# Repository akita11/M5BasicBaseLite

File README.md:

# M5BasicBaseLite

M5Stackの上部本体(Core Basic)にとりつけて、以下のようなM5GO/Fireの機能やそれ以外の機能を追加できる底板（ベースボード）用の拡張基板です。
[M5GOBaseLite](https://github.com/akita11/M5GOBaseLite)の後継機で、基本的な機能・回路は同一で、裏面のメスMbusコネクタが使えるようになりました。
- Groveコネクタ(PortA(2個), PortB, PortC, PortD, PortE)（PortA/B/CはM5Stack純正のものと同等です。PortD/EはM5Stack純正品にはありませんが、UI Flowで使用することができるポートです）
- 左右5個ずつのNeoPixel (SK6812)（オプション）
- LiPoバッテリ接続端子（オプション）

# 使い方
1. M5Stackの本体(Core、底板を外した状態)に本ボードを差し込みます。
2. M5Stackのプログラムから、Groveコネクタに接続したセンサ類を使用します。
   - 各Groveコネクタのピン配置は以下の通り（中央寄りのVDDから近い側、遠い側の順）
     - PortA: GPIO21(SDA), GPIO22(SCL)
     - PortB: GPIO26, GPIO36
     - PortC: GPIO17(TXD2), GPIO16(RXD2)
     - PortD: GPIO35, GPIO34
     - PortE: GPIO13, GPIO5
   - （オプション）左右のNeoPixelの制御信号はGPIO15につながっています。UI Flowでは、Hardware→RGB LED、から使用できます

# 底面カバー

[M5GOBaseLite](https://github.com/akita11/M5GOBaseLite)用のカバーを使用できます。

# Author

Junichi Akita (@akita11, akita@ifdl.jp)

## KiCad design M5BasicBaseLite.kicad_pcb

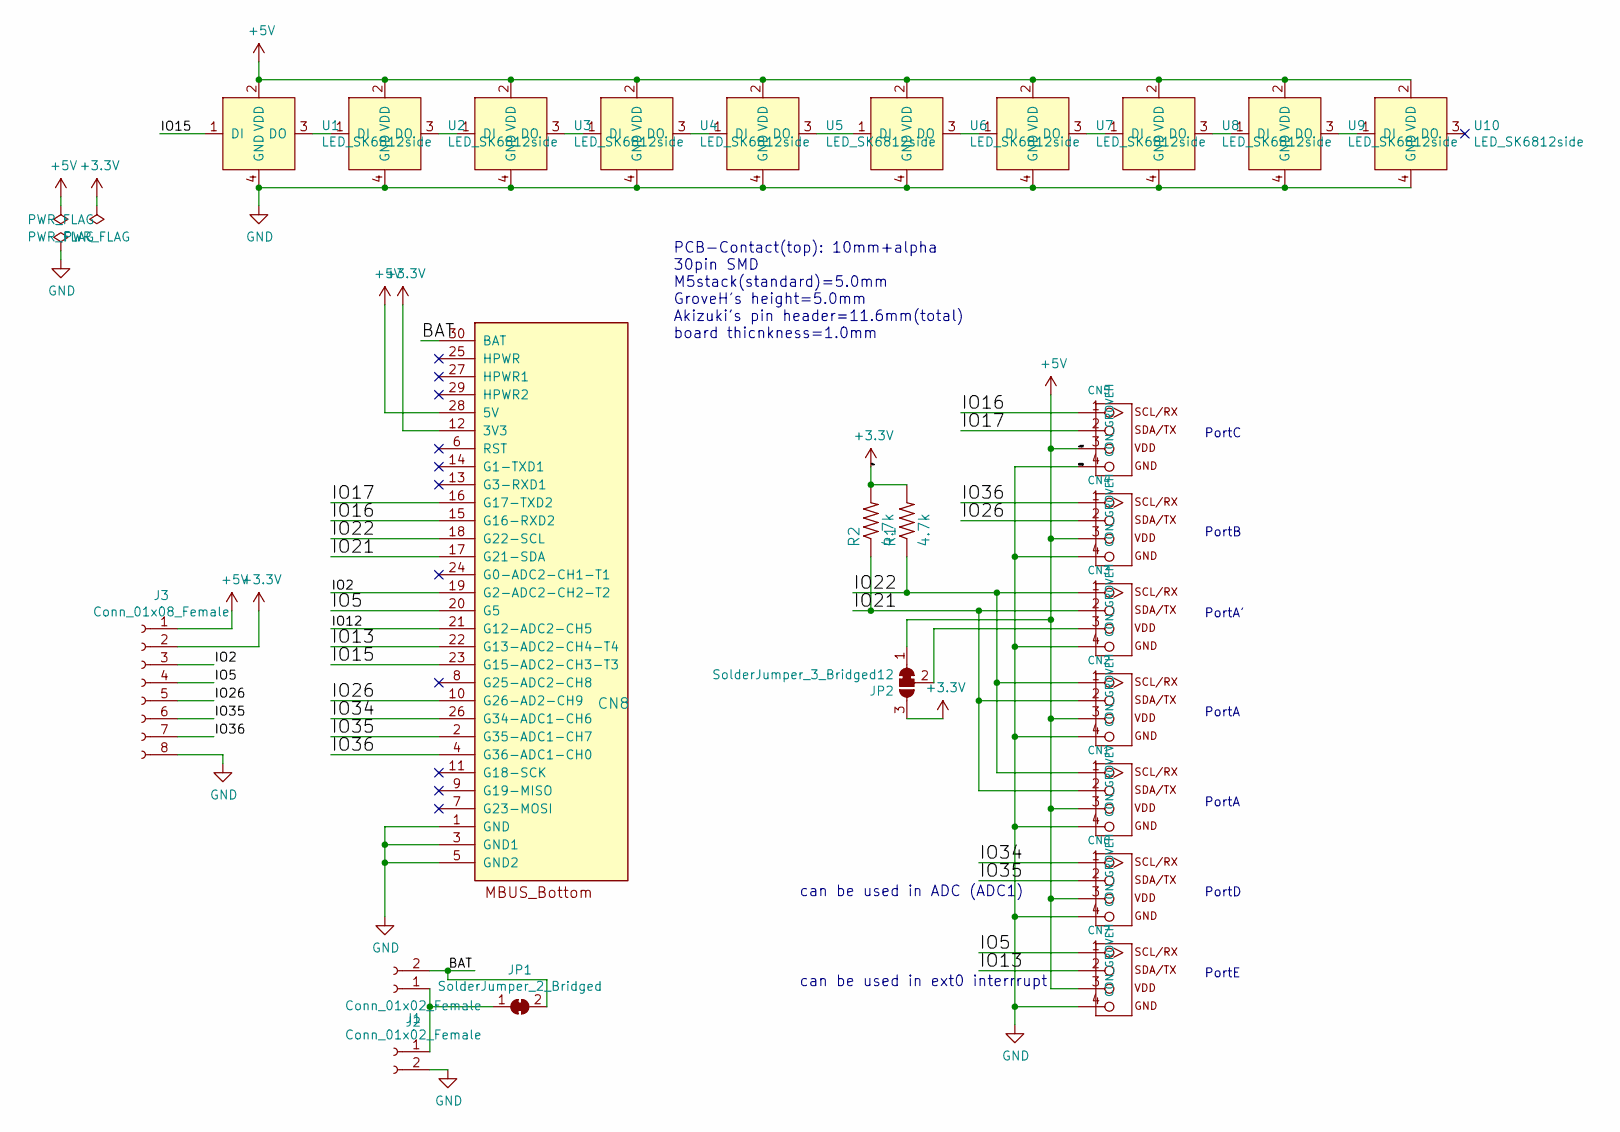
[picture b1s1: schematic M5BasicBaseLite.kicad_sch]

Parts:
CN1: CON_GROVEV; CON_GROVE_V
CN2, CN3, CN4, CN5, CN6, CN7: CON_GROVEH; CON_GROVE_H
CN8: MBUS_bottom; PinSocket_2x15_P2.54mm_Vertical_SMD
J1: Conn_01x02_Female; JST_PH_S2B-PH-K_1x02_P2.00mm_Horizontal
J2: Conn_01x02_Female; PinHeader_1x02_P2.54mm_Horizontal
J3: Conn_01x08_Female; PinSocket_1x08_P2.54mm_Horizontal
JP1: SolderJumper_2_Bridged; SolderJumper-2_P1.3mm_Bridged_Pad1.0x1.5mm
JP2: SolderJumper_3_Bridged12; SolderJumper-3_P1.3mm_Bridged2Bar12_Pad1.0x1.5mm
R1, R2: 4.7k; 0603
U1, U2, U3, U4, U5, U6, U7, U8, U9, U10: LED_SK6812side; LED_SK6812SIDE

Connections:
+3V3: CN8.12 (3V3), J3.2, JP2.3 (B), R1.2, R2.2; also elsewhere on the board
+5V: CN1.3, CN2.3, CN4.3, CN5.3, CN6.3, CN7.3, CN8.28 (5V), J3.1, JP2.1 (A), U1.2 (VDD), U2.2 (VDD), U3.2 (VDD), U4.2 (VDD), U5.2 (VDD), U6.2 (VDD), U7.2 (VDD), U8.2 (VDD), U9.2 (VDD), U10.2 (VDD); also elsewhere on the board
/BAT: CN8.30 (BAT), J2.2, JP1.2 (B)
/IO2: CN8.19 (G2-ADC2-CH2-T2), J3.3; also elsewhere on the board
/IO5: CN7.1, CN8.20 (G5), J3.4; also elsewhere on the board
/IO12: CN8.21 (G12-ADC2-CH5); also elsewhere on the board
/IO13: CN7.2, CN8.22 (G13-ADC2-CH4-T4); also elsewhere on the board
/IO15: CN8.23 (G15-ADC2-CH3-T3), U1.1 (DI); also elsewhere on the board
/IO16: CN5.1, CN8.15 (G16-RXD2); also elsewhere on the board
/IO17: CN5.2, CN8.16 (G17-TXD2); also elsewhere on the board
/IO21: CN1.2, CN2.2, CN3.2, CN8.17 (G21-SDA), R2.1; also elsewhere on the board
/IO22: CN1.1, CN2.1, CN3.1, CN8.18 (G22-SCL), R1.1; also elsewhere on the board
/IO26: CN4.2, CN8.10 (G26-AD2-CH9), J3.5; also elsewhere on the board
/IO34: CN6.1, CN8.26 (G34-ADC1-CH6); also elsewhere on the board
/IO35: CN6.2, CN8.2 (G35-ADC1-CH7), J3.6; also elsewhere on the board
/IO36: CN4.1, CN8.4 (G36-ADC1-CH0), J3.7; also elsewhere on the board
GND: CN1.4, CN2.4, CN3.4, CN4.4, CN5.4, CN6.4, CN7.4, CN8.1 (GND), CN8.3 (GND1), CN8.5 (GND2), J1.2, J3.8, U1.4 (GND), U2.4 (GND), U3.4 (GND), U4.4 (GND), U5.4 (GND), U6.4 (GND), U7.4 (GND), U8.4 (GND), U9.4 (GND), U10.4 (GND); also elsewhere on the board
unnamed: CN3.3, JP2.2 (C)
unnamed 29: J1.1, J2.1, JP1.1 (A); also elsewhere on the board
unnamed: U1.3 (DO), U2.1 (DI)
unnamed: U2.3 (DO), U3.1 (DI)
unnamed: U3.3 (DO), U4.1 (DI)
unnamed: U4.3 (DO), U5.1 (DI)
unnamed: U5.3 (DO), U6.1 (DI)
unnamed: U6.3 (DO), U7.1 (DI)
unnamed: U7.3 (DO), U8.1 (DI)
unnamed: U8.3 (DO), U9.1 (DI)
unnamed: U9.3 (DO), U10.1 (DI)

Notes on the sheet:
PortA
can be used in ADC (ADC1)
PCB-Contact(top): 10mm+alpha 30pin SMD M5stack(standard)=5.0mm GroveH's height=5.0mm Akizuki's pin header=11.6mm(total) board thicnkness=1.0mm
PortE
PortC
PortA'
PortB
can be used in ext0 interrrupt
PortD

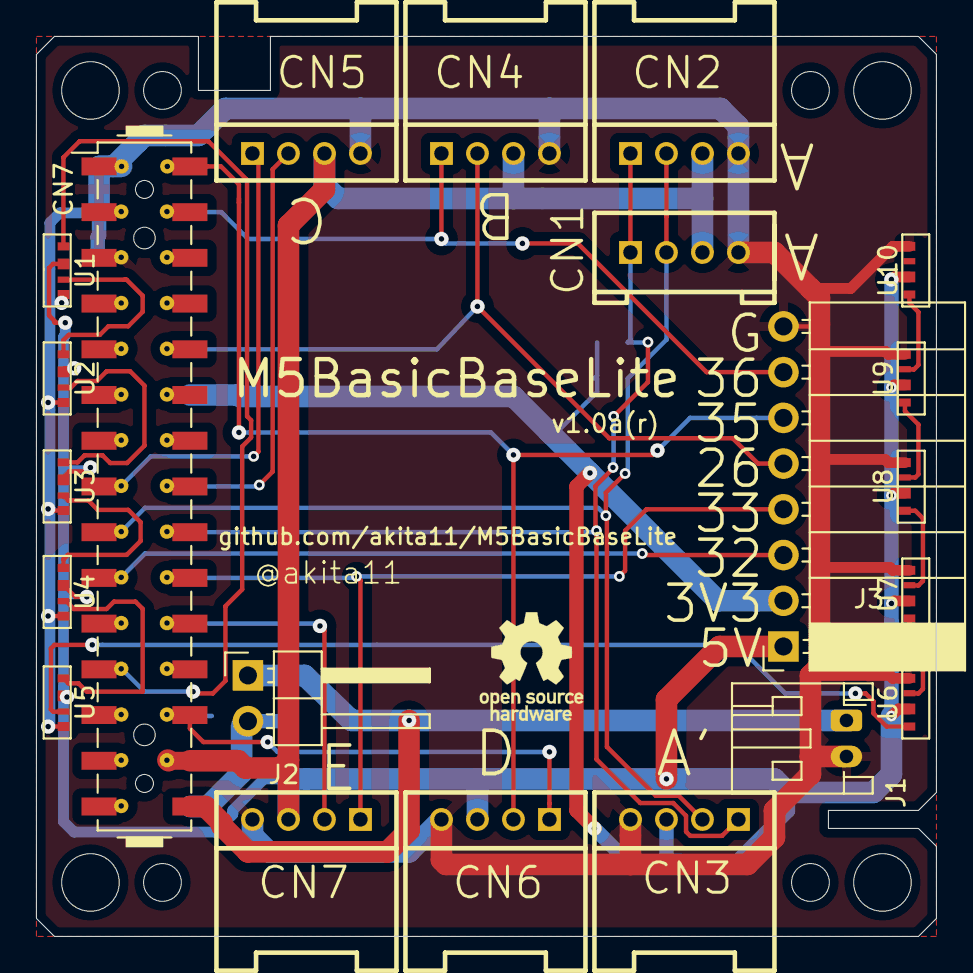
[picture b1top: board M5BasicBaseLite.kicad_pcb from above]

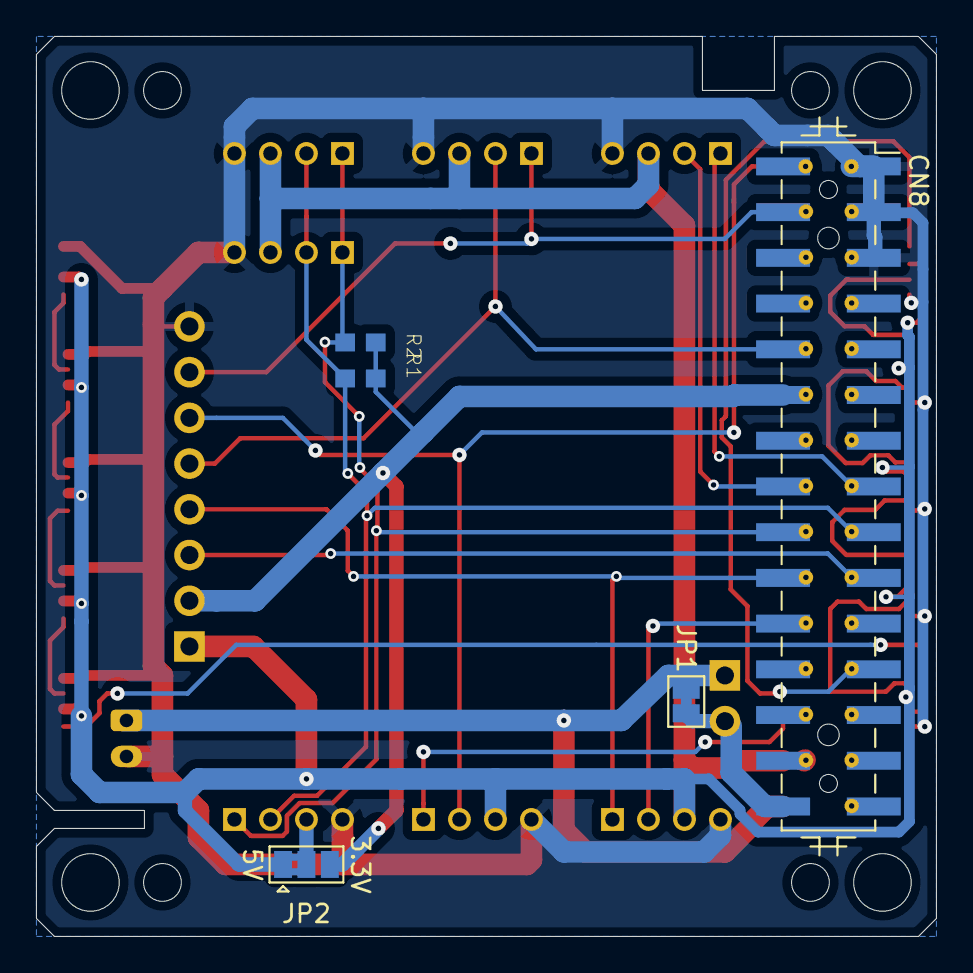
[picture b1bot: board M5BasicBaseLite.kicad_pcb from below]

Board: 2 copper layers, 50.0 x 50.0 mm, 34 parts (5 on the bottom side), 28 nets.

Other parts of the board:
CN7#2: PinHeader_2x15_P2.54mm_Vertical_SMD
MH1, MH1#2, MH1#3, MH2: MountingHole_3.2mm_M3
MH5, MH5#2, MH5#3, MH5#4: MountingHole_2.1mm

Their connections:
+3V3: CN7#2.12; also elsewhere on the board
+5V: CN7#2.28; also elsewhere on the board
/IO2: CN7#2.19; also elsewhere on the board
/IO5: CN7#2.20; also elsewhere on the board
/IO12: CN7#2.21; also elsewhere on the board
/IO13: CN7#2.22; also elsewhere on the board
/IO15: CN7#2.23; also elsewhere on the board
/IO16: CN7#2.15; also elsewhere on the board
/IO17: CN7#2.16; also elsewhere on the board
/IO21: CN7#2.17; also elsewhere on the board
/IO22: CN7#2.18; also elsewhere on the board
/IO26: CN7#2.10; also elsewhere on the board
/IO34: CN7#2.26; also elsewhere on the board
/IO35: CN7#2.2; also elsewhere on the board
/IO36: CN7#2.4; also elsewhere on the board
GND: CN7#2.1, CN7#2.3, CN7#2.5; also elsewhere on the board
unnamed 29: CN7#2.30; also elsewhere on the board

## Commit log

2023-01-20 add data files
2023-01-20 copy README from M5GOBaseLite
2023-01-21 add images
